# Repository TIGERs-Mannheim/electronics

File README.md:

# TIGERs Mannheim Open-Source Electronics

This repository contains electronics for our robots and our base station. There is one folder for each released version.  
Have a look at our [2020 ETDP](https://tigers-mannheim.de/download/tdps/2020_ETDP_TIGERS.pdf) which contains many details about design decisions and lessons learned over the last 10 years.

The following files are present for each release.

### EAGLE
Electronics are designed with [Autodesk EAGLE](https://www.autodesk.com/education/free-software/eagle) which is available for free for students.
This folder contains all schematics (.sch) and board (.brd) files.

### KiCad9
EAGLE files converted to KiCad version 9. Files got only a light cleanup pass.
Note that no PCBs were ever produced using these files. The EAGLE files are still the ground truth.

### PDF
All schematics are also available as PDF files. This makes it easier to view them without a need to install EAGLE.

### CAM
CAM jobs for EAGLE. Used to produce manufacturing data from board files.

### Gerber
Production ready zip packages for all boards. Most PCB production services directly accept gerber files.

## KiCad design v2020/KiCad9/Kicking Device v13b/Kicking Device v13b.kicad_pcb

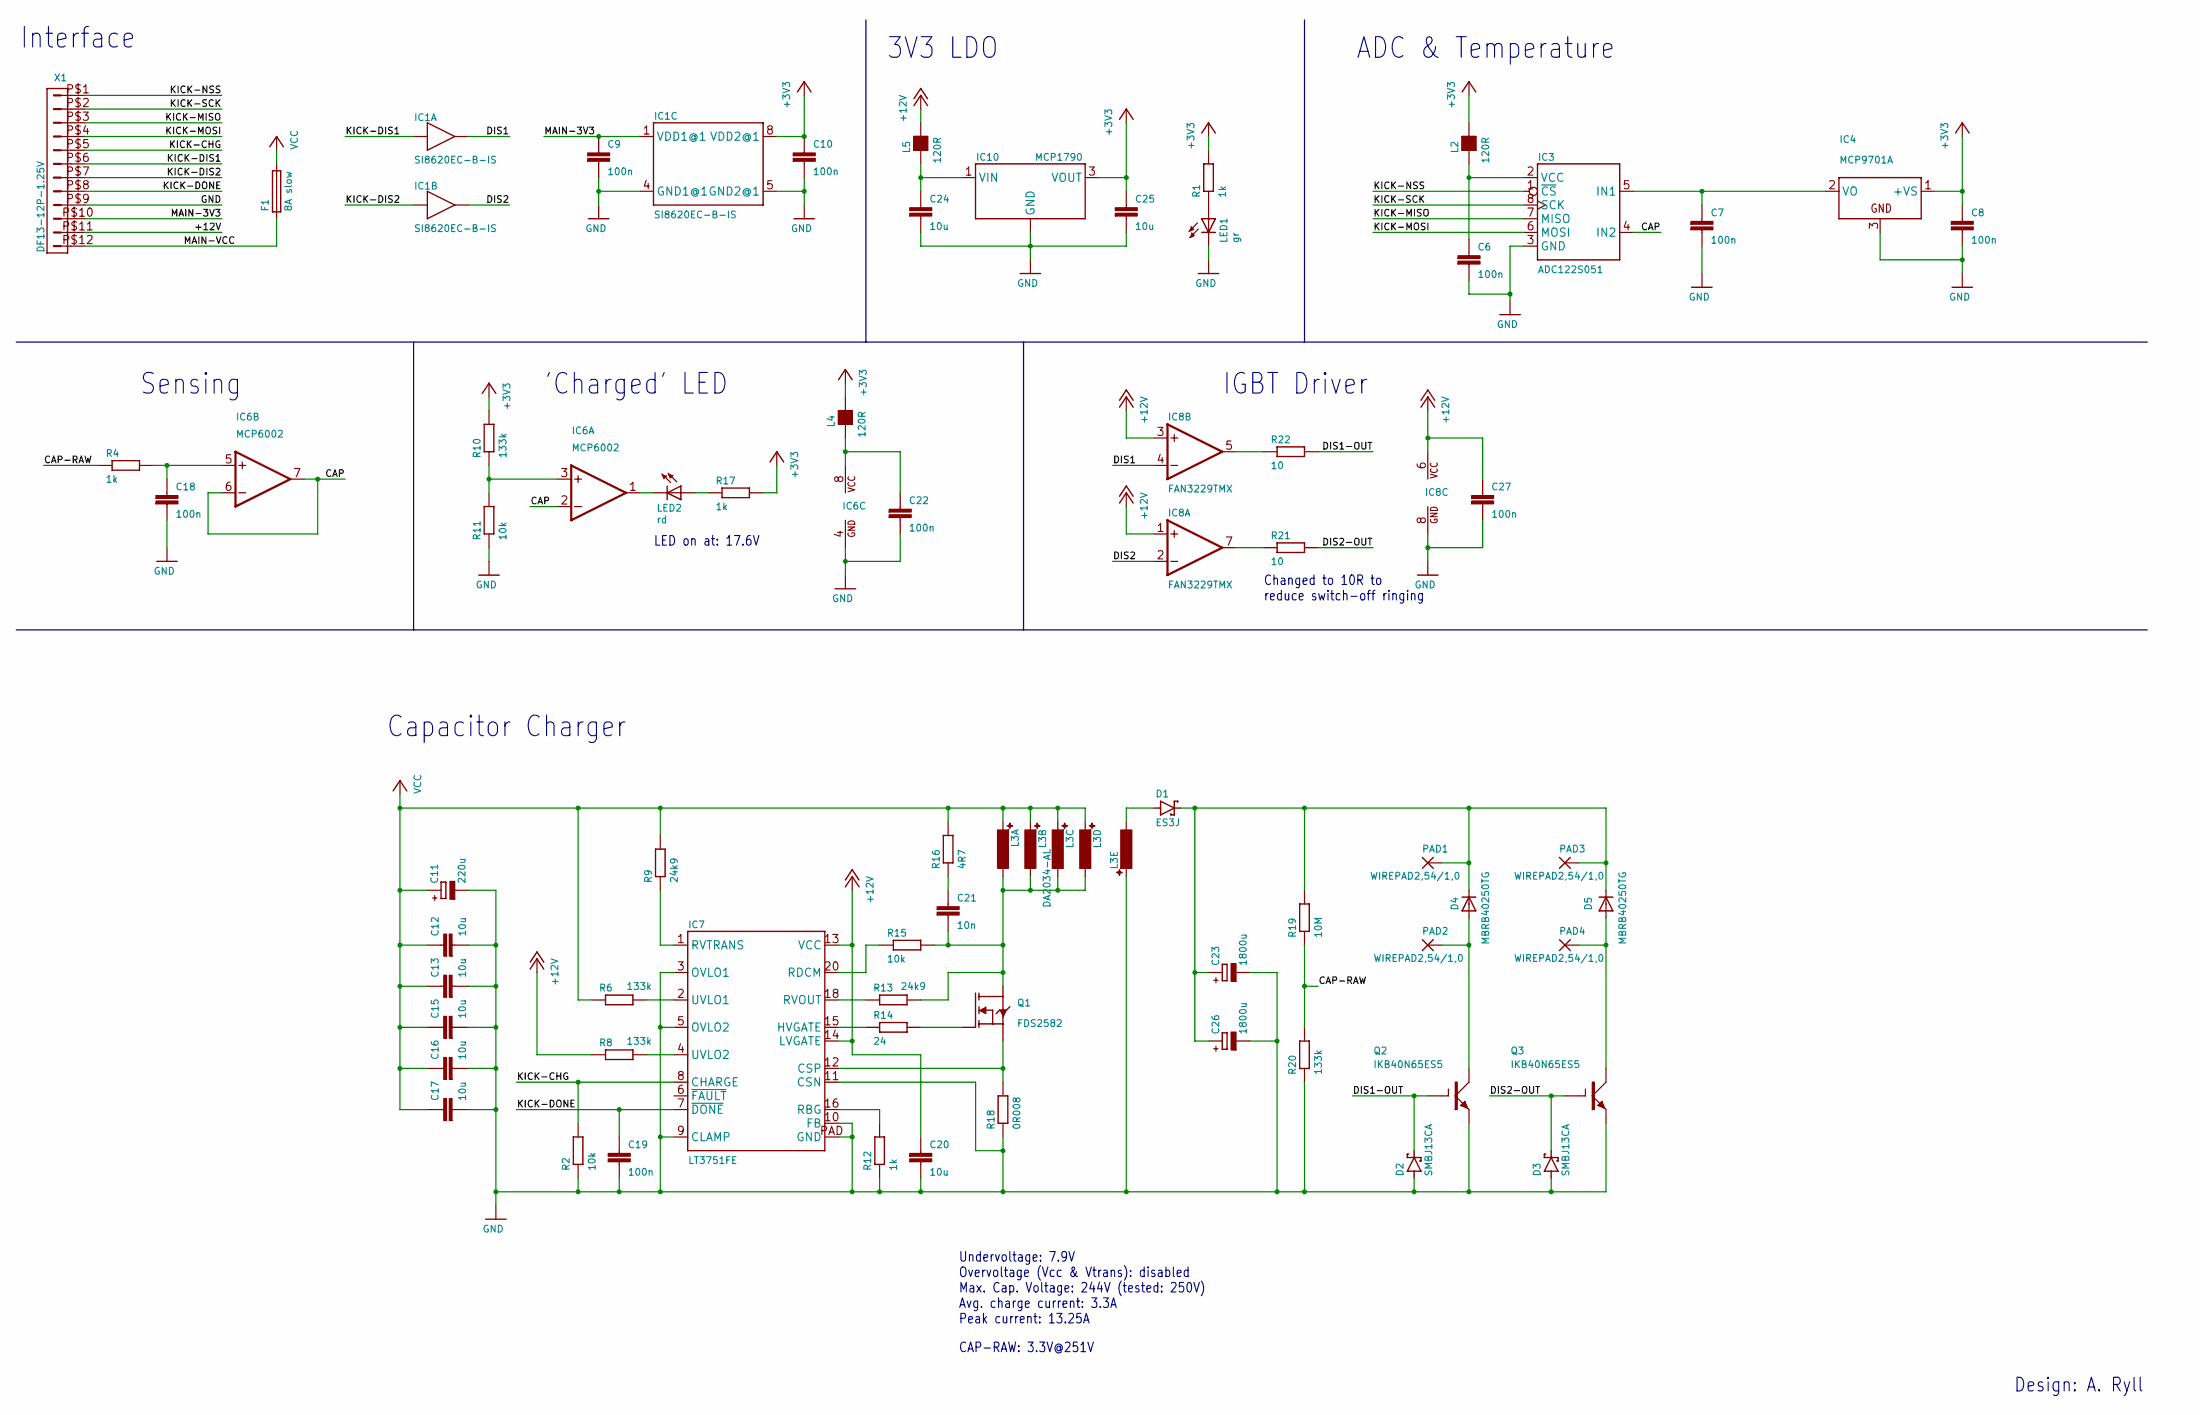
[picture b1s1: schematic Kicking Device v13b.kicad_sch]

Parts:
C6, C7, C8, C9, C10, C18, C19, C22, C27: 100n; C0603; Digi-Key 1292-1397-1-ND
C11: 220u; PANASONIC_F; Mfg Part # EEEFT1H221AP; Digi-Key PCE5025CT-ND
C12, C13, C15, C16, C17: 10u; C1210; Mfg Part # C3225X5R1H106M250AB; Digi-Key 1276-6736-2-ND
C20, C24, C25: 10u; C0603; Digi-Key 490-12737-1-ND
C21: 10n; C0805
C23, C26: 1800u; EB35D; Digi-Key 493-7224-ND
D1: ES3J; SMC; Digi-Key ES3JCT-ND
D2, D3: SMBJ13CA; SMB; Digi-Key SMBJ13CA-FDICT-ND
D4, D5: MBRB40250TG; D2PAK; Digi-Key MBRB40250TGOS-ND
F1: 8A slow; 1206; Digi-Key 507-1194-1-ND
IC1: SI8620EC-B-IS; SOIC8N; Digi-Key 336-2062-5-ND
IC3: ADC122S051; MSOP8; Digi-Key ADC122S051CIMM/NOPBCT-ND
IC4: MCP9701A; SOT23; Digi-Key MCP9701AT-E/TTCT-ND
IC6: MCP6002; SOIC8N; Digi-Key MCP6002T-I/SNCT-ND
IC7: LT3751FE; TSSOP20P; Digi-Key LT3751EFE#PBF-ND
IC8: FAN3229TMX; SOIC8N; Digi-Key FAN3229TMXCT-ND
IC10: MCP1790; SOT223; Digi-Key MCP1790-3302E/DB-ND
L2, L4, L5: 120R; L0603; Digi-Key 490-1037-1-ND
L3: DA2034-AL; Mfg Part # DA2034-AL
LED1: gr; CHIP-LED0603; Digi-Key 732-4980-1-ND
LED2: rd; CHIP-LED0603; Digi-Key 732-4979-1-ND
PAD1, PAD2, PAD3, PAD4: WIREPAD2,54/1,0; 2,54_1,0
Q1: FDS2582; SOIC8N; Digi-Key FDS2582CT-ND
Q2, Q3: IKB40N65ES5; D2PAK; Digi-Key IKB40N65ES5ATMA1CT-ND
R1, R4, R12, R17: 1k; R0603; Digi-Key 311-1.00KHRCT-ND
R2, R11, R15: 10k; R0603; Digi-Key 311-10.0KHRCT-ND
R6, R8, R10, R20: 133k; R0603; Digi-Key P133KDBCT-ND
R9, R13: 24k9; R0603; Digi-Key P24.9KHCT-ND
R14: 24; R1206
R16: 4R7; R0805; Digi-Key RHM4.7KCT-ND
R18: 0R008; R1206; Digi-Key RHM.008ALCT-ND
R19: 10M; R1206; Digi-Key 541-10MBACT-ND
R21, R22: 10; R1206
X1: DF13-12P-1.25V; DF13C-12P-1.25V; Digi-Key H121957CT-ND

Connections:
+3V3: C8.1, C10.1, C25.1, IC1.8 (VDD2@1), IC4.1 (+VS), IC10.3 (VOUT), L2.2, L4.2, R1.2, R10.2, R17.2
+12V: C20.1, C27.1, IC7.13 (VCC), IC7.14 (LVGATE), IC8.1 (+IN), IC8.3 (+IN), IC8.6 (VCC), L5.2, R8.1, X1.P$11 (11)
/CAP: IC3.4 (IN2), IC6.2 (-IN), IC6.6 (-IN), IC6.7 (OUT)
/CAP-RAW: R4.1, R19.1, R20.2
/DIS1: IC1.7 (OUT), IC8.4 (-IN)
/DIS1-OUT: D2.C, Q2.1 (G), R22.2
/DIS2: IC1.6 (OUT), IC8.2 (-IN)
/DIS2-OUT: D3.C, Q3.1 (G), R21.2
/KICK-CHG: IC7.8 (CHARGE), R2.2, X1.P$5 (5)
/KICK-DIS1: IC1.2 (IN), X1.P$6 (6)
/KICK-DIS2: IC1.3 (IN), X1.P$7 (7)
/KICK-DONE: C19.1, IC7.7 (~DONE), X1.P$8 (8)
/KICK-MISO: IC3.7 (MISO), X1.P$3 (3)
/KICK-MOSI: IC3.6 (MOSI), X1.P$4 (4)
/KICK-NSS: IC3.1 (~CS), X1.P$1 (1)
/KICK-SCK: IC3.8 (SCK), X1.P$2 (2)
/MAIN-3V3: C9.1, IC1.1 (VDD1@1), X1.P$10 (10)
/MAIN-VCC: F1.1, X1.P$12 (12)
GND: C6.2, C7.2, C8.2, C9.2, C10.2, C11.-, C12.2, C13.2, C15.2, C16.2, C17.2, C18.2, C19.2, C20.2, C22.2, C23.-, C24.2, C25.2, C26.-, C27.2, D2.A, D3.A, IC1.4 (GND1@1), IC1.5 (GND2@1), IC3.3 (GND), IC4.3 (GND), IC6.4 (GND), IC7.3 (OVLO1), IC7.5 (OVLO2), IC7.9 (CLAMP), IC7.10 (FB), IC7.11 (CSN), IC7.PAD (GND), IC8.8 (GND), IC10.2 (GND), IC10.4 (GND), L3.12 (2), LED1.C, Q2.3 (E), Q3.3 (E), R2.1, R11.1, R12.1, R18.1, R20.1, X1.P$9 (9)
unnamed: C21.1, R16.1
unnamed: D1.A, L3.1
unnamed: C23.+, C26.+, D1.C, D4.2 (C), D5.2 (C), PAD1.1, PAD3.1, R19.2
unnamed: C7.1, IC3.5 (IN1), IC4.2 (VO)
unnamed: C6.1, IC3.2 (VCC), L2.1
unnamed: IC6.3 (+IN), R10.1, R11.2
unnamed: IC6.1 (OUT), LED2.C
unnamed: C18.1, IC6.5 (+IN), R4.2
unnamed: C22.1, IC6.8 (VCC), L4.1
unnamed: IC7.12 (CSP), Q1.1 (S), Q1.2 (S), Q1.3 (S), R18.2
unnamed: IC7.15 (HVGATE), R14.1
unnamed: IC7.16 (RBG), R12.2
unnamed: IC7.20 (RDCM), R15.1
unnamed: IC7.18 (RVOUT), R13.1
unnamed: IC7.1 (RVTRANS), R9.1
unnamed: IC7.2 (UVLO1), R6.2
unnamed: IC7.4 (UVLO2), R8.2
unnamed: IC8.7 (OUT), R21.1
unnamed: IC8.5 (OUT), R22.1
unnamed: C24.1, IC10.1 (VIN), L5.1
unnamed: C21.2, L3.7 (1), L3.8 (1), L3.9 (1), L3.10 (1), Q1.5 (D), Q1.6 (D), Q1.7 (D), Q1.8 (D), R13.2, R15.2
unnamed: LED1.A, R1.1
unnamed: LED2.A, R17.1
unnamed: D4.1 (A), D4.3 (A), PAD2.1, Q2.2 (C)
unnamed: D5.1 (A), D5.3 (A), PAD4.1, Q3.2 (C)
unnamed: Q1.4 (G), R14.2
VCC: C11.+, C12.1, C13.1, C15.1, C16.1, C17.1, F1.2, L3.3 (2), L3.4 (2), L3.5 (2), L3.6 (2), R6.1, R9.2, R16.2

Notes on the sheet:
Undervoltage: 7.9V Overvoltage (Vcc & Vtrans): disabled Max. Cap. Voltage: 244V (tested: 250V) Avg. charge current: 3.3A Peak current: 13.25A
Capacitor Charger
3V3 LDO
LED on at: 17.6V
Changed to 10R to reduce switch-off ringing
ADC & Temperature
Design: A. Ryll
Sensing
CAP-RAW: 3.3V@251V
Interface
IGBT Driver
'Charged' LED

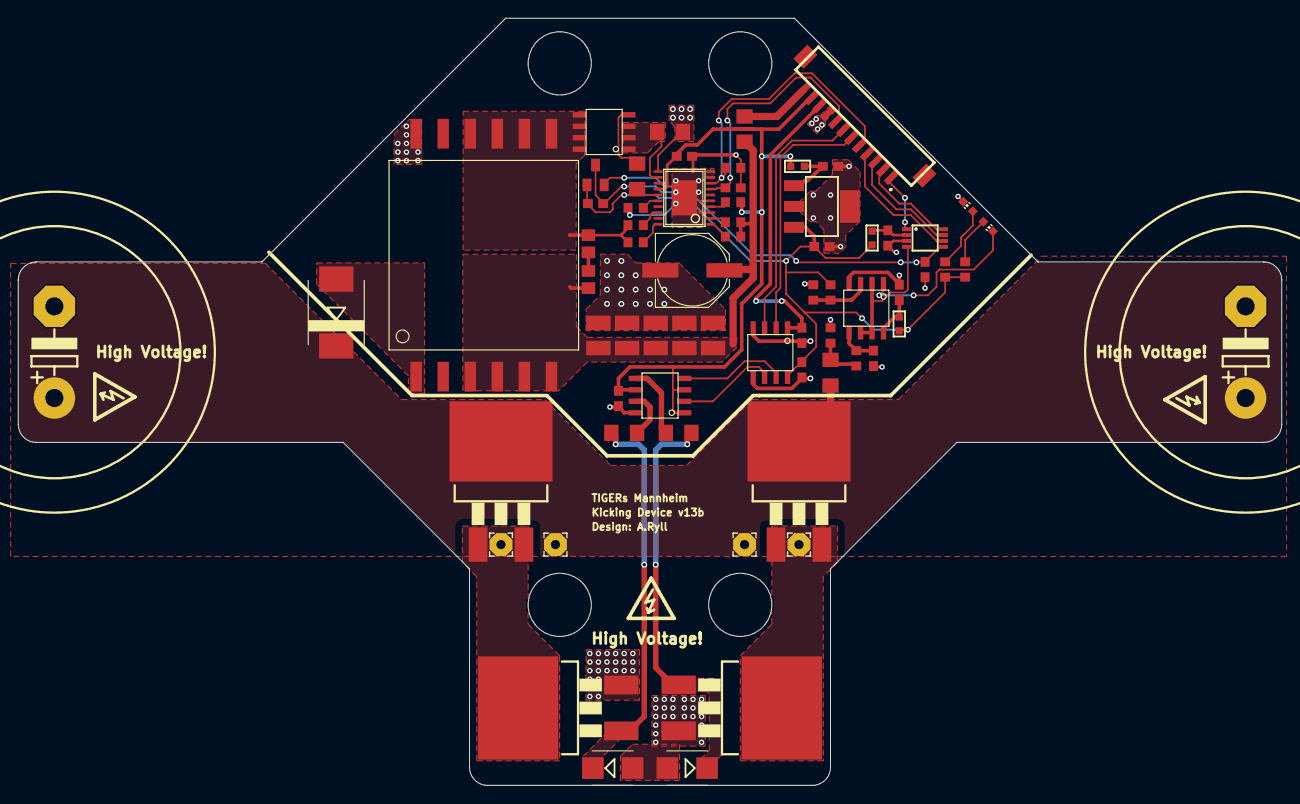
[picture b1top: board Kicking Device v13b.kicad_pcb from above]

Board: 2 copper layers, 140.0 x 85.0 mm, 71 parts (0 on the bottom side), 46 nets.

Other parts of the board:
UNK_HOLE_0: dummyfp0
UNK_HOLE_1: dummyfp1
UNK_HOLE_2: dummyfp2
UNK_HOLE_3: dummyfp3

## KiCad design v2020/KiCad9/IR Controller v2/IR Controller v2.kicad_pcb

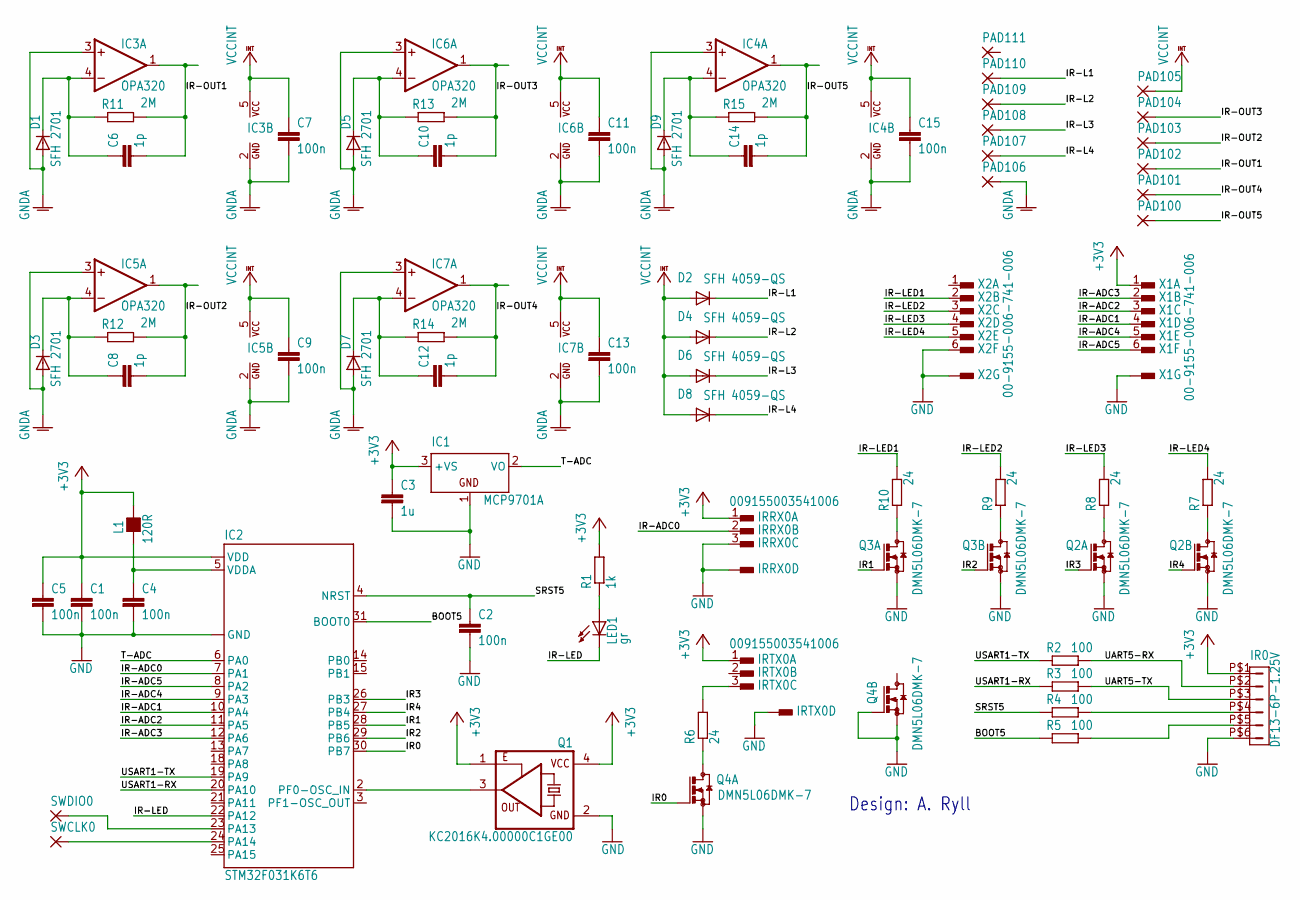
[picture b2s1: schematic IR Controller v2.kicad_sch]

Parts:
C1, C2, C4, C5, C7, C9, C11, C13, C15: 100n; C0603
C3: 1u; C0603
C6, C8, C10, C12, C14: 1p; C0603
D1, D3, D5, D7, D9: SFH 2701; LED-GULL
D2, D4, D6, D8: SFH 4059-QS; LED-GULL
IC1: MCP9701A; TO92
IC2: STM32F031K6T6; LQFP32-ST
IC3, IC4, IC5, IC6, IC7: OPA320; SOT23-5
IR0: DF13-6P-1.25V; DF13C-6P-1.25V
IRRX0: 009155003541006; AVX-CON3
IRTX0: 009155003541006; AVX-CON3
L1: 120R; L0603
LED1: gr; CHIP-LED0603
PAD100, PAD101, PAD102, PAD103, PAD104, PAD105, PAD106, PAD107, PAD108, PAD109, PAD110, PAD111: WIREPADSMD1,4-3; SMD1,4-3
Q1: KC2016K4.00000C1GE00; OSCI-KC2016
Q2, Q3, Q4: DMN5L06DMK-7; SOT26
R1: 1k; R0603
R2, R3, R4, R5: 100; R0805
R6, R7, R8, R9, R10: 24; R0805
R11, R12, R13, R14, R15: 2M; R0603
SWCLK0: WIREPADSMD1,27-254; SMD1,27-2,54
SWDIO0: WIREPADSMD1,27-254; SMD1,27-2,54
X1, X2: 00-9155-006-741-006; AVX-CON6-2MM

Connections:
+3V3: C1.1, C3.1, C5.1, IC1.3 (+VS), IC2.1 (VDD), IC2.17 (VDD), IR0.P$1 (1), IRRX0.1, IRTX0.1, L1.2, Q1.1 (OE), Q1.4 (VCC), R1.2, X1.1
BOOT5: IC2.31 (BOOT0), R5.1
GND: C1.2, C2.2, C3.2, C4.2, C5.2, IC1.1 (GND), IC2.16 (GND), IC2.32 (GND), IR0.P$6 (6), IRRX0.3, IRRX0.S1, IRRX0.S2, IRTX0.S1, IRTX0.S2, Q1.2 (GND), Q2.1 (S), Q2.4 (S), Q3.1 (S), Q3.4 (S), Q4.1 (S), Q4.2 (G), Q4.4 (S), X1.S1, X1.S2, X2.6, X2.S1, X2.S2
GNDA: C7.2, C9.2, C11.2, C13.2, C15.2, D1.A, D3.A, D5.A, D7.A, D9.A, IC3.2 (GND), IC3.3 (+IN), IC4.2 (GND), IC4.3 (+IN), IC5.2 (GND), IC5.3 (+IN), IC6.2 (GND), IC6.3 (+IN), IC7.2 (GND), IC7.3 (+IN), PAD106.1
IR0: IC2.30 (PB7), Q4.5 (G)
IR1: IC2.28 (PB5), Q3.5 (G)
IR2: IC2.29 (PB6), Q3.2 (G)
IR3: IC2.26 (PB3), Q2.5 (G)
IR4: IC2.27 (PB4), Q2.2 (G)
IR-ADC0: IC2.7 (PA1), IRRX0.2
IR-ADC1: IC2.10 (PA4), X1.4
IR-ADC2: IC2.11 (PA5), X1.3
IR-ADC3: IC2.12 (PA6), X1.2
IR-ADC4: IC2.9 (PA3), X1.5
IR-ADC5: IC2.8 (PA2), X1.6
IR-L1: D2.C, PAD110.1
IR-L2: D4.C, PAD109.1
IR-L3: D6.C, PAD108.1
IR-L4: D8.C, PAD107.1
IR-LED: IC2.22 (PA12), LED1.C
IR-LED1: R10.2, X2.2
IR-LED2: R9.2, X2.3
IR-LED3: R8.2, X2.4
IR-LED4: R7.2, X2.5
IR-OUT1: C6.2, IC3.1 (OUT), PAD102.1, R11.2
IR-OUT2: C8.2, IC5.1 (OUT), PAD103.1, R12.2
IR-OUT3: C10.2, IC6.1 (OUT), PAD104.1, R13.2
IR-OUT4: C12.2, IC7.1 (OUT), PAD101.1, R14.2
IR-OUT5: C14.2, IC4.1 (OUT), PAD100.1, R15.2
unnamed: IR0.P$4 (4), R4.2
unnamed: IC2.23 (PA13), SWDIO0.1
unnamed: IR0.P$5 (5), R5.2
unnamed: IC2.24 (PA14), SWCLK0.1
unnamed: C14.1, D9.C, IC4.4 (-IN), R15.1
unnamed: C10.1, D5.C, IC6.4 (-IN), R13.1
unnamed: C8.1, D3.C, IC5.4 (-IN), R12.1
unnamed: Q3.3 (D), R10.1
unnamed: C6.1, D1.C, IC3.4 (-IN), R11.1
unnamed: IC2.2 (PF0-OSC_IN), Q1.3 (FO)
unnamed: C4.1, IC2.5 (VDDA), L1.1
unnamed: IRTX0.3, R6.2
unnamed: C12.1, D7.C, IC7.4 (-IN), R14.1
unnamed: Q4.3 (D), R6.1
unnamed: Q3.6 (D), R9.1
unnamed: Q2.3 (D), R8.1
unnamed: Q2.6 (D), R7.1
unnamed: LED1.A, R1.1
SRST5: C2.1, IC2.4 (NRST), R4.1
T-ADC: IC1.2 (VO), IC2.6 (PA0)
UART5-RX: IR0.P$2 (2), R2.2
UART5-TX: IR0.P$3 (3), R3.2
USART1-RX: IC2.20 (PA10), R3.1
USART1-TX: IC2.19 (PA9), R2.1
VCCINT: C7.1, C9.1, C11.1, C13.1, C15.1, D2.A, D4.A, D6.A, D8.A, IC3.5 (VCC), IC4.5 (VCC), IC5.5 (VCC), IC6.5 (VCC), IC7.5 (VCC), PAD105.1

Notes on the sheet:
Design: A. Ryll

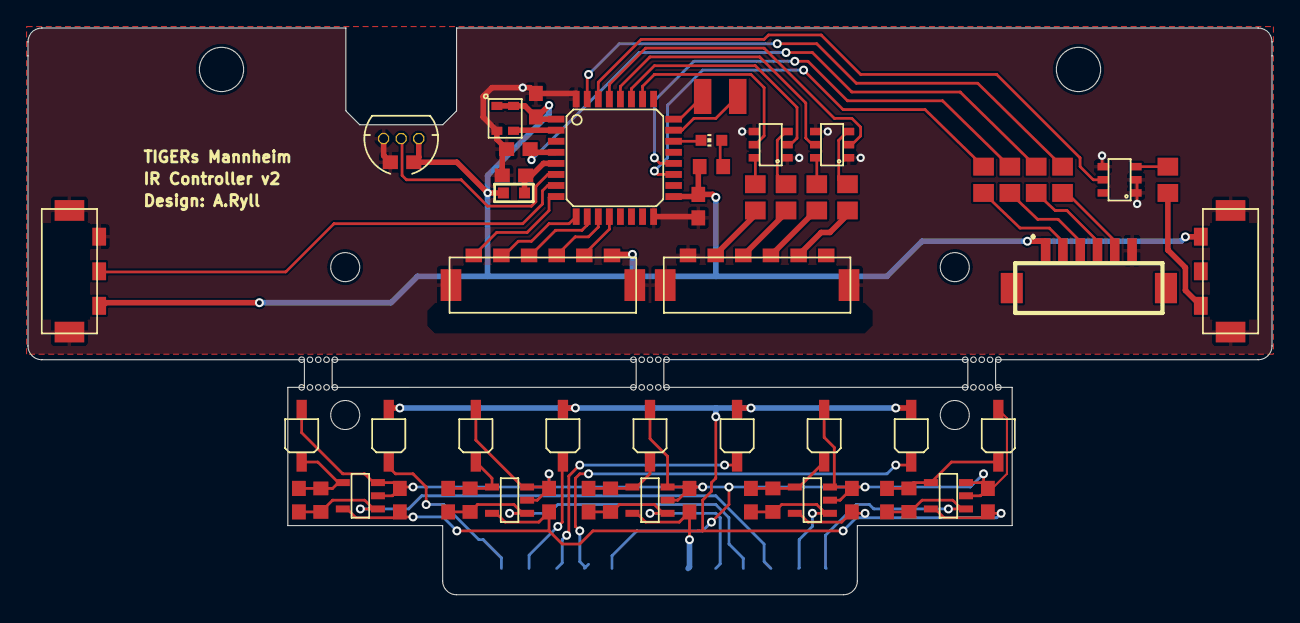
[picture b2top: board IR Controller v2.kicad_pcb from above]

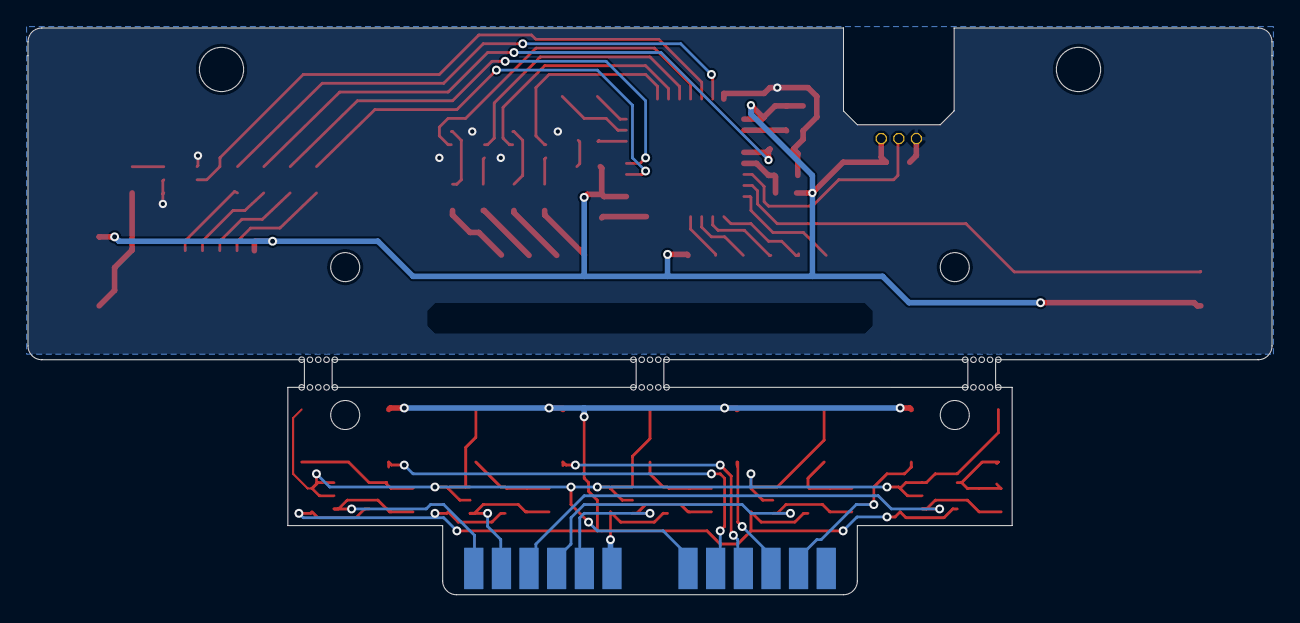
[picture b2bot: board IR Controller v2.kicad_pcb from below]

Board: 2 copper layers, 90.0 x 41.0 mm, 107 parts (12 on the bottom side), 54 nets.

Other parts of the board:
UNK_HOLE_0: dummyfp0
UNK_HOLE_1: dummyfp1
UNK_HOLE_2: dummyfp2
UNK_HOLE_3: dummyfp3
UNK_HOLE_4: dummyfp4
UNK_HOLE_5: dummyfp5
UNK_HOLE_6: dummyfp6
UNK_HOLE_7: dummyfp7
UNK_HOLE_8: dummyfp8
UNK_HOLE_9: dummyfp9
UNK_HOLE_10: dummyfp10
UNK_HOLE_11: dummyfp11
UNK_HOLE_12: dummyfp12
UNK_HOLE_13: dummyfp13
UNK_HOLE_14: dummyfp14
UNK_HOLE_15: dummyfp15
UNK_HOLE_16: dummyfp16
UNK_HOLE_17: dummyfp17
UNK_HOLE_18: dummyfp18
UNK_HOLE_19: dummyfp19
UNK_HOLE_20: dummyfp20
UNK_HOLE_21: dummyfp21
UNK_HOLE_22: dummyfp22
UNK_HOLE_23: dummyfp23
UNK_HOLE_24: dummyfp24
UNK_HOLE_25: dummyfp25
UNK_HOLE_26: dummyfp26
UNK_HOLE_27: dummyfp27
UNK_HOLE_28: dummyfp28
UNK_HOLE_29: dummyfp29
UNK_HOLE_30: dummyfp30
UNK_HOLE_31: dummyfp31
UNK_HOLE_32: dummyfp32
UNK_HOLE_33: dummyfp33
UNK_HOLE_34: dummyfp34
UNK_HOLE_35: dummyfp35

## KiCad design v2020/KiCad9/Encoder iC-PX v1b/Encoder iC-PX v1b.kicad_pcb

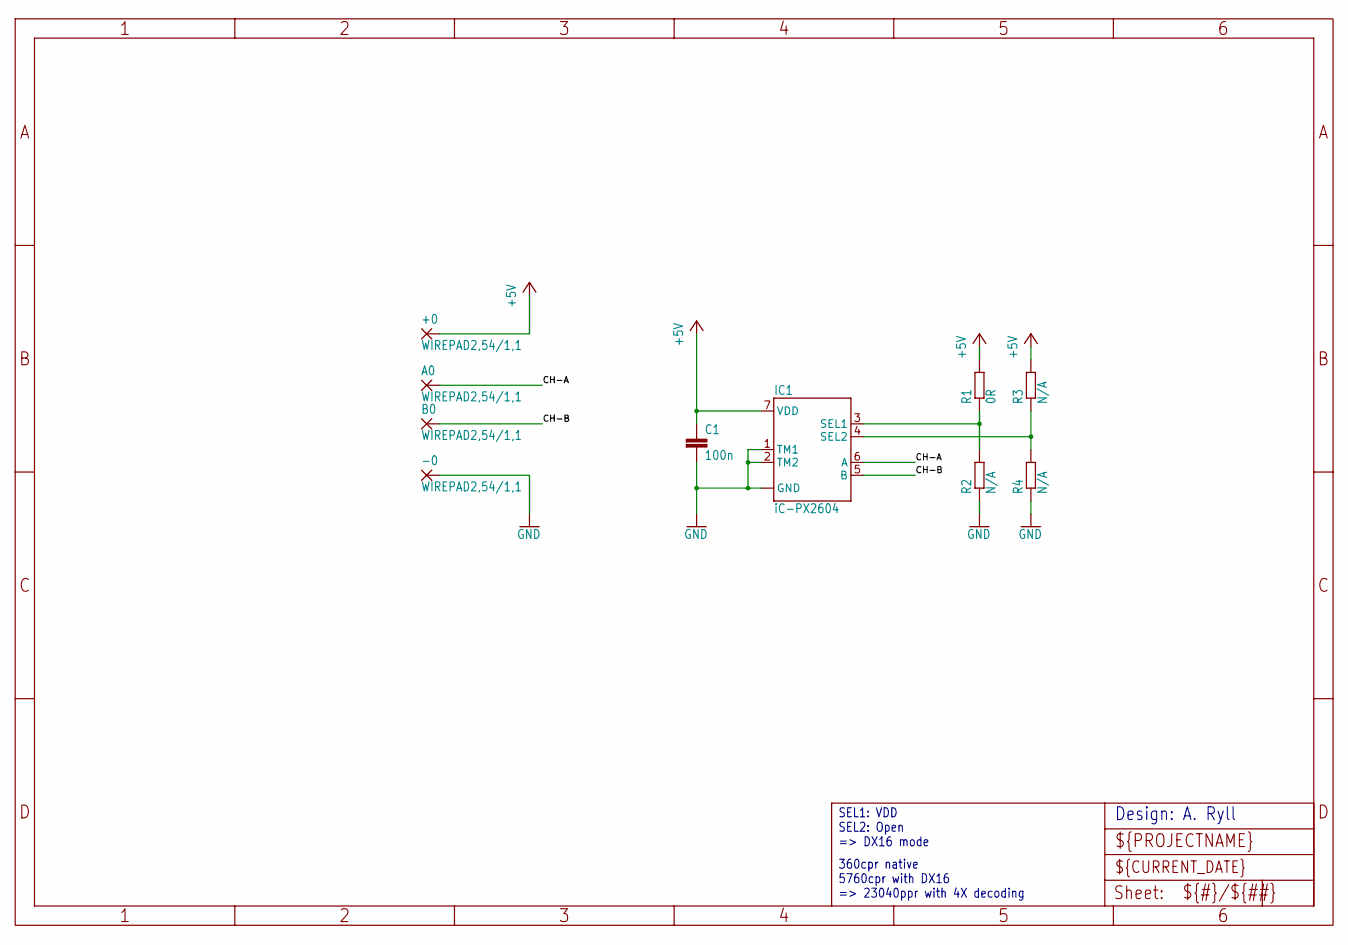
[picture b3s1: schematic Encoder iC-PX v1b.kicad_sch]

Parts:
+0: WIREPAD2,54/1,1; 2,54_1,1
-0: WIREPAD2,54/1,1; 2,54_1,1
A0: WIREPAD2,54/1,1; 2,54_1,1
B0: WIREPAD2,54/1,1; 2,54_1,1
C1: 100n; C0603
IC1: iC-PX2604; ODFN8-3X3
R1: 0R; R0603
R2, R3, R4: N/A; R0603

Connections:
+5V: +0.1, C1.1, IC1.7 (VDD), R1.2, R3.2
CH-A: A0.1, IC1.6 (A)
CH-B: B0.1, IC1.5 (B)
GND: -0.1, C1.2, IC1.1 (TM1), IC1.2 (TM2), IC1.8 (GND), IC1.BP (GND), R2.1, R4.1
SEL1: IC1.3 (SEL1), R1.1, R2.2
SEL2: IC1.4 (SEL2), R3.1, R4.2

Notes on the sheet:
360cpr native 5760cpr with DX16 => 23040ppr with 4X decoding
SEL1: VDD SEL2: Open => DX16 mode
Design: A. Ryll

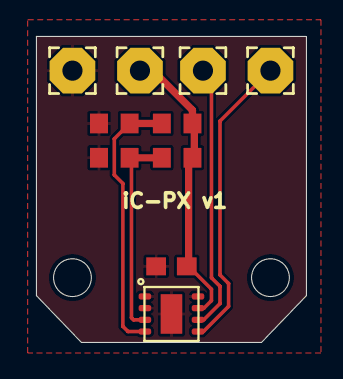
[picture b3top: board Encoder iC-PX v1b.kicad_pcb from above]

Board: 2 copper layers, 15.0 x 17.0 mm, 12 parts (0 on the bottom side), 6 nets.

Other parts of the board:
UNK_HOLE_0: dummyfp0
UNK_HOLE_1: dummyfp1

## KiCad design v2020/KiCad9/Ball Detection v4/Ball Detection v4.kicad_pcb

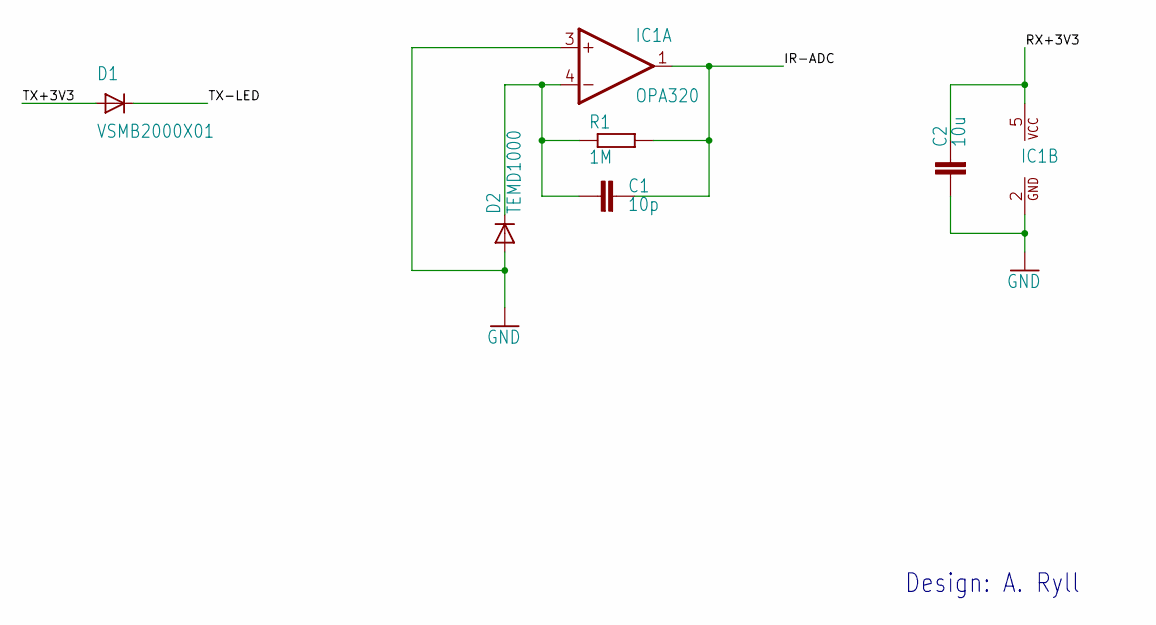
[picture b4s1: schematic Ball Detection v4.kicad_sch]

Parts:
C1: 10p; C0603
C2: 10u; C0603
D1: VSMB2000X01; LED-GULLR
D2: TEMD1000; LED-GULLR
IC1: OPA320; SOT23-5
R1: 1M; R0603

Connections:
GND: C2.1, D2.A, IC1.2 (GND), IC1.3 (+IN)
IR-ADC: C1.2, IC1.1 (OUT), R1.2
unnamed: C1.1, D2.C, IC1.4 (-IN), R1.1
NC: D1.C
RX+3V3: C2.2, IC1.5 (VCC)
TX-LED: D1.A

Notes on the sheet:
Design: A. Ryll

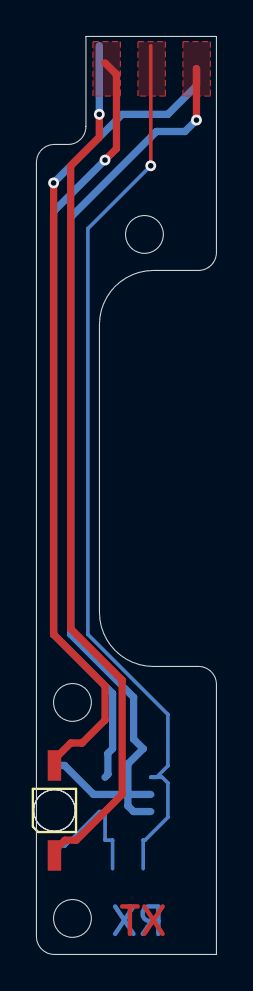
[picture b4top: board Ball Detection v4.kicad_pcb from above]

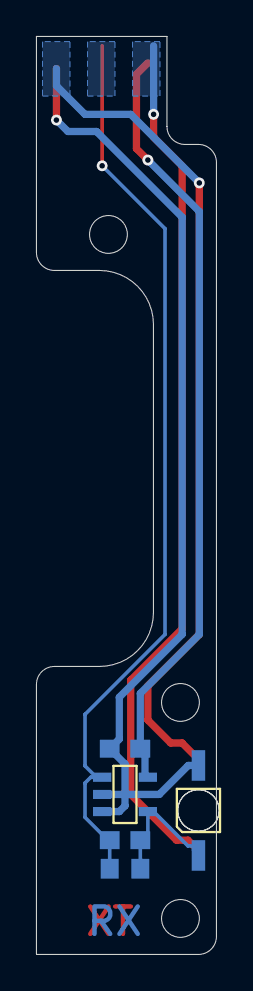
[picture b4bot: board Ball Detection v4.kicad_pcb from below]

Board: 2 copper layers, 10.0 x 51.0 mm, 9 parts (5 on the bottom side), 4 nets.

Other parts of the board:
UNK_HOLE_0: dummyfp0
UNK_HOLE_1: dummyfp1
UNK_HOLE_2: dummyfp2

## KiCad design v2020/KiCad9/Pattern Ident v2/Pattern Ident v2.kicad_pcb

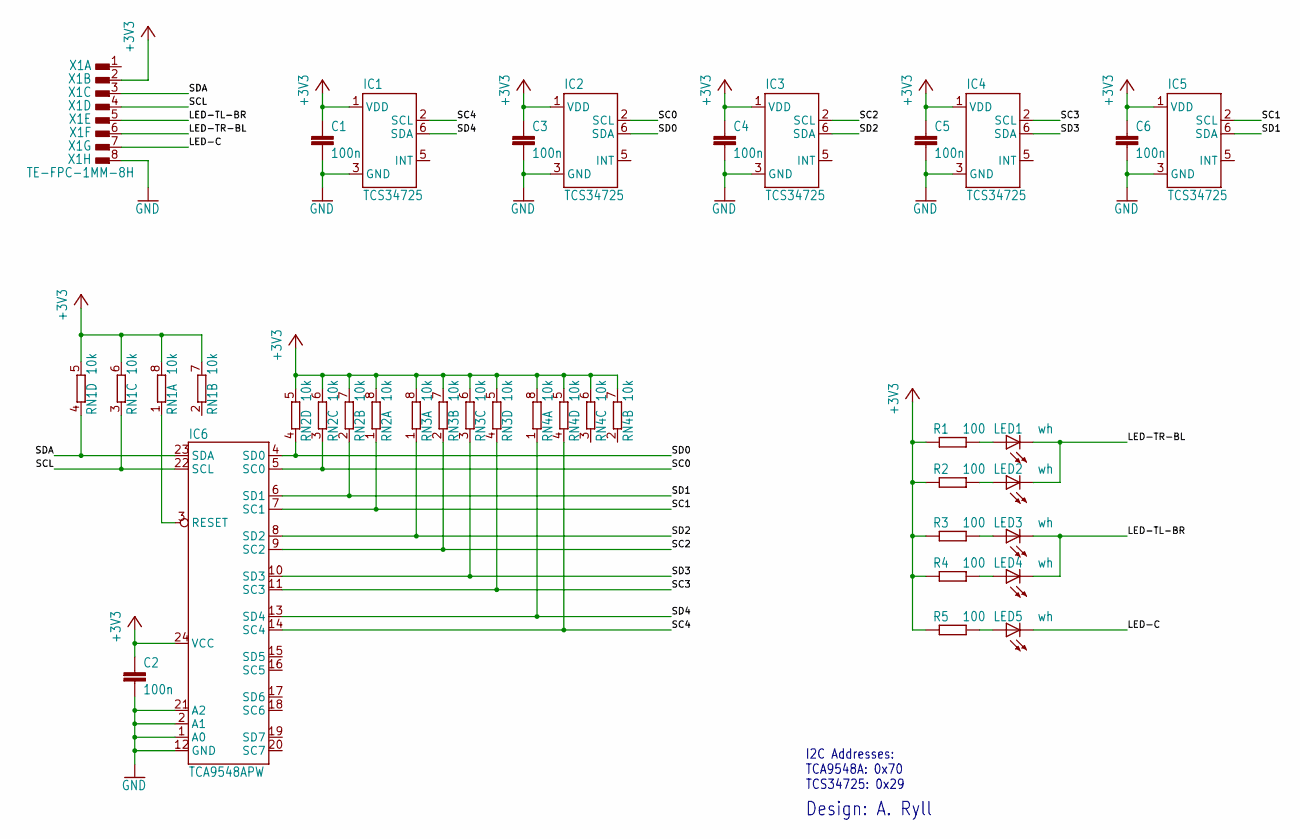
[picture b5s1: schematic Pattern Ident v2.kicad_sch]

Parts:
C1, C2, C3, C4, C5, C6: 100n; C0603
IC1, IC2, IC3, IC4, IC5: TCS34725; DFN6
IC6: TCA9548APW; TSSOP24
LED1, LED2, LED3, LED4, LED5: wh; CHIPLED_1206
R1, R2, R3, R4, R5: 100; R0603
RN1, RN2, RN3, RN4: 10k; EXB28V
X1: TE-FPC-1MM-8H; TE-84952-8

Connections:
+3V3: C1.1, C2.1, C3.1, C4.1, C5.1, C6.1, IC1.1 (VDD), IC2.1 (VDD), IC3.1 (VDD), IC4.1 (VDD), IC5.1 (VDD), IC6.24 (VCC), R1.1, R2.1, R3.1, R4.1, R5.1, RN1.5 (2), RN1.6 (2), RN1.7 (2), RN1.8 (2), RN2.5 (2), RN2.6 (2), RN2.7 (2), RN2.8 (2), RN3.5 (2), RN3.6 (2), RN3.7 (2), RN3.8 (2), RN4.5 (2), RN4.6 (2), RN4.7 (2), RN4.8 (2), X1.2
GND: C1.2, C2.2, C3.2, C4.2, C5.2, C6.2, IC1.3 (GND), IC2.3 (GND), IC3.3 (GND), IC4.3 (GND), IC5.3 (GND), IC6.1 (A0), IC6.2 (A1), IC6.12 (GND), IC6.21 (A2), X1.8
LED-C: LED5.C, X1.7
LED-TL-BR: LED3.C, LED4.C, X1.5
LED-TR-BL: LED1.C, LED2.C, X1.6
unnamed: LED1.A, R1.2
unnamed: LED2.A, R2.2
unnamed: LED3.A, R3.2
unnamed: LED4.A, R4.2
unnamed: LED5.A, R5.2
RESET: IC6.3 (RESET), RN1.1
SC0: IC2.2 (SCL), IC6.5 (SC0), RN2.3 (1)
SC1: IC5.2 (SCL), IC6.7 (SC1), RN2.1
SC2: IC3.2 (SCL), IC6.9 (SC2), RN3.2 (1)
SC3: IC4.2 (SCL), IC6.11 (SC3), RN3.4 (1)
SC4: IC1.2 (SCL), IC6.14 (SC4), RN4.4 (1)
SCL: IC6.22 (SCL), RN1.3 (1), X1.4
SD0: IC2.6 (SDA), IC6.4 (SD0), RN2.4 (1)
SD1: IC5.6 (SDA), IC6.6 (SD1), RN2.2 (1)
SD2: IC3.6 (SDA), IC6.8 (SD2), RN3.1
SD3: IC4.6 (SDA), IC6.10 (SD3), RN3.3 (1)
SD4: IC1.6 (SDA), IC6.13 (SD4), RN4.1
SDA: IC6.23 (SDA), RN1.4 (1), X1.3

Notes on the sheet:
I2C Addresses: TCA9548A: 0x70 TCS34725: 0x29
Design: A. Ryll

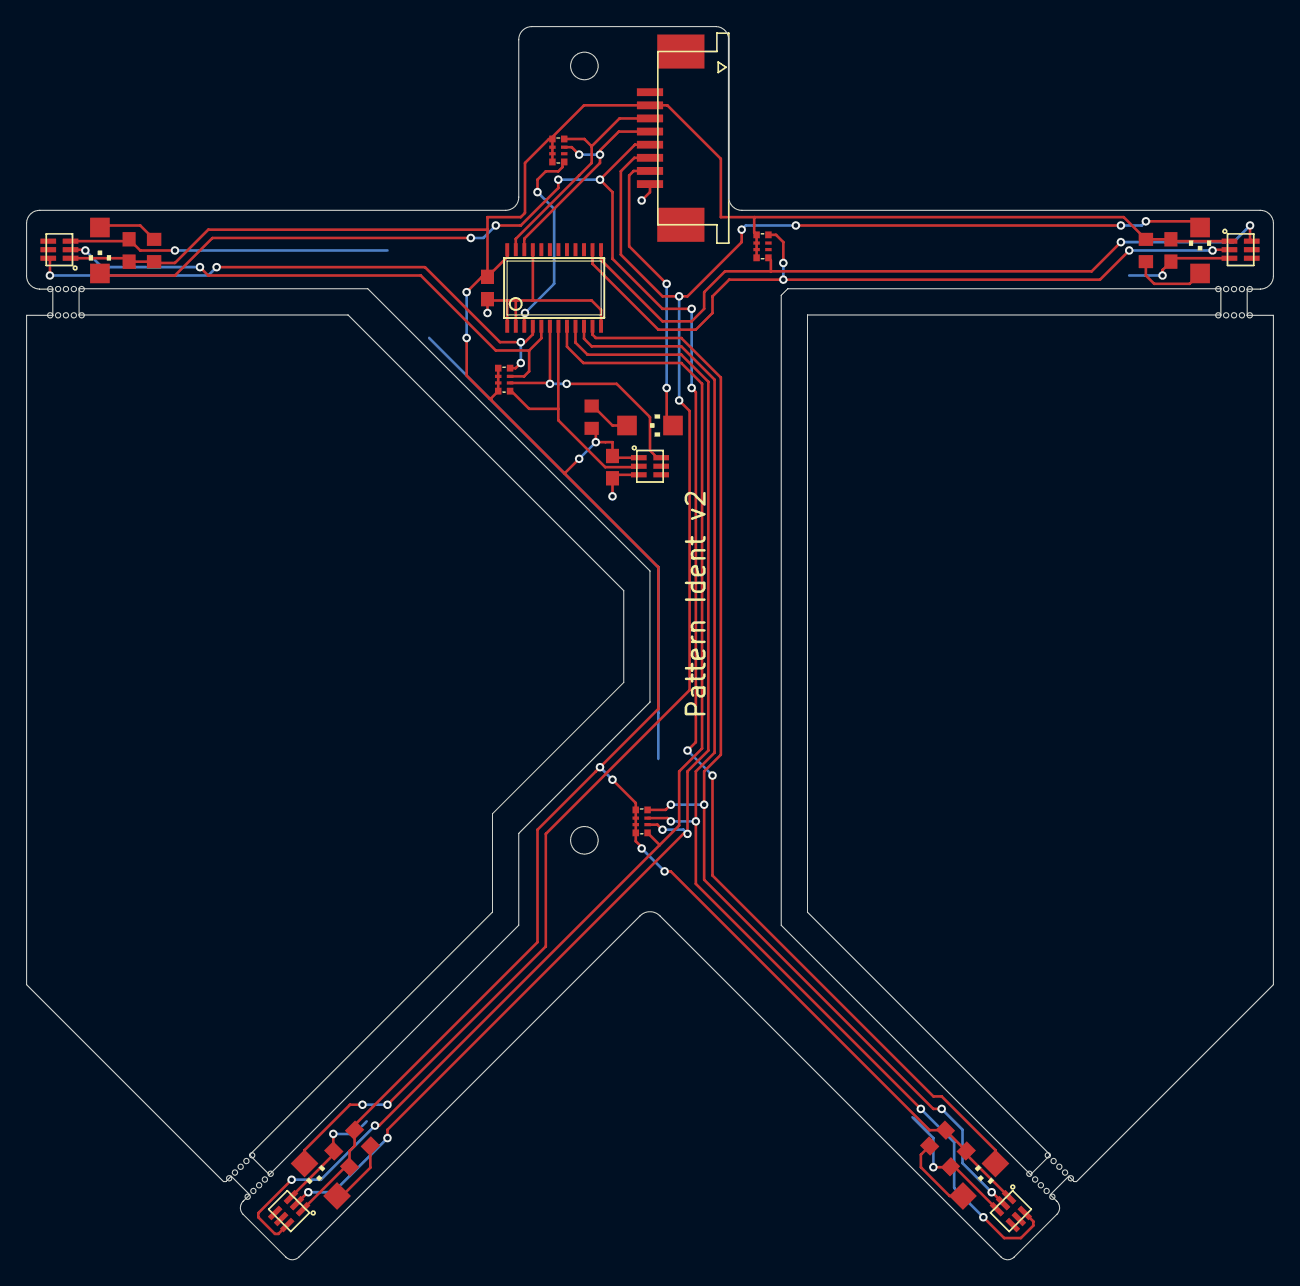
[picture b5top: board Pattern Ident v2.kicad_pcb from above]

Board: 2 copper layers, 95.0 x 94.0 mm, 69 parts (0 on the bottom side), 23 nets.

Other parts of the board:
UNK_HOLE_0: dummyfp0
UNK_HOLE_1: dummyfp1
UNK_HOLE_2: dummyfp2
UNK_HOLE_3: dummyfp3
UNK_HOLE_4: dummyfp4
UNK_HOLE_5: dummyfp5
UNK_HOLE_6: dummyfp6
UNK_HOLE_7: dummyfp7
UNK_HOLE_8: dummyfp8
UNK_HOLE_9: dummyfp9
UNK_HOLE_10: dummyfp10
UNK_HOLE_11: dummyfp11
UNK_HOLE_12: dummyfp12
UNK_HOLE_13: dummyfp13
UNK_HOLE_14: dummyfp14
UNK_HOLE_15: dummyfp15
UNK_HOLE_16: dummyfp16
UNK_HOLE_17: dummyfp17
UNK_HOLE_18: dummyfp18
UNK_HOLE_19: dummyfp19
UNK_HOLE_20: dummyfp20
UNK_HOLE_21: dummyfp21
UNK_HOLE_22: dummyfp22
UNK_HOLE_23: dummyfp23
UNK_HOLE_24: dummyfp24
UNK_HOLE_25: dummyfp25
UNK_HOLE_26: dummyfp26
UNK_HOLE_27: dummyfp27
UNK_HOLE_28: dummyfp28
UNK_HOLE_29: dummyfp29
UNK_HOLE_30: dummyfp30
UNK_HOLE_31: dummyfp31
UNK_HOLE_32: dummyfp32
UNK_HOLE_33: dummyfp33
UNK_HOLE_34: dummyfp34
UNK_HOLE_35: dummyfp35
UNK_HOLE_36: dummyfp36
UNK_HOLE_37: dummyfp37
UNK_HOLE_38: dummyfp38
UNK_HOLE_39: dummyfp39
UNK_HOLE_40: dummyfp40
UNK_HOLE_41: dummyfp41
